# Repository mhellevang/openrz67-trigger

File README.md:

# openrz67-trigger

A Bluetooth remote release for the Mamiya RZ67. A small box on a coin cell plugs into the
camera's remote port. An Android or iPhone app fires the shutter, holds it open for bulb, or
runs a countdown.

## What it does

- Instant release, bulb, and a countdown of 1 to 255 seconds.
- Runs on a CR2032. It sleeps between uses and wakes on a button press.
- Nothing to solder. The board comes assembled from JLCPCB, everything else plugs in.
- Firmware updates over Bluetooth.

## Build one

> **Work in progress.** This board is rev B. It fixes the two known faults in rev A, but is not
> tested yet. For a board that is tested and in use, build the larger ESP32-C3 version at tag
> [`esp32-final`](https://github.com/mhellevang/openrz67-trigger/tree/esp32-final/esp32):
> order the files in
> [`esp32/pcb/archive/2026-09-07-rev2/`](https://github.com/mhellevang/openrz67-trigger/tree/esp32-final/esp32/pcb/archive/2026-09-07-rev2),
> not the rev 3 source. It runs on a LiPo, charges and flashes over USB-C, and works with the
> same apps.

**→ [Build guide](docs/build-guide.md)**: parts, ordering the board, printing the case,
flashing, the camera cable.

In short:

1. Order the assembled board from JLCPCB with the files in [`kicad/out/`](kicad/out/).
2. Print the case from [`case/`](case/).
3. Flash the firmware once with a Raspberry Pi Pico. After that, updates go over Bluetooth.
4. Make the camera cable from a Qwiic pigtail.
5. Install the app.

## Apps

- **Android:** [openrz67-android](https://github.com/mhellevang/openrz67-android), APK on the
  [releases page](https://github.com/mhellevang/openrz67-android/releases/latest).
- **iPhone:** [openrz67-ios](https://github.com/mhellevang/openrz67-ios), built from source in
  Xcode for now.

## Using it

| You do | It does |
|---|---|
| Press the button | Wakes and waits 3 minutes for a phone. The LED blinks every 2 s |
| Open the app | Connects on its own. The LED goes dark |
| Leave it | Stays on while the app is connected. With no phone for 3 minutes, it sleeps |
| Hold the button 3 s | Off, until the next press |

For bulb, set the camera's shutter-speed dial to `B`. The camera closes the shutter by itself
after about 60 seconds.

## What's in here

```
openrz67-trigger/
├── kicad/        # the board, generated from tools/design.py; fab files in out/
├── case/         # 3D-printed case (build123d), shell + sliding floor + light pipe; STLs in stl/
├── firmware/     # Zephyr application for the nRF54L15
└── docs/
    ├── build-guide.md
    ├── protocol.md     # camera port and Bluetooth commands
    ├── perfboard.md    # the same circuit on perfboard, off-the-shelf parts
    ├── support.md      # app help
    ├── privacy.md      # app privacy policy
    ├── render/         # renders docs/img/case-*.png with Blender
    └── notes/          # design history and reasoning
```

Earlier ESP32-C3 versions are at tag
[`esp32-final`](https://github.com/mhellevang/openrz67-trigger/tree/esp32-final/esp32).

## License

[MIT](LICENSE), covering the firmware, the KiCad design files and the enclosure sources. MIT
is written for software, but its grant is broad enough to serve a hardware design;
the closest hardware-specific equivalent is CERN-OHL-P.

The footprints, symbols and 3D models in `kicad/openrz67-nrf.pretty/`,
`openrz67-nrf.kicad_sym` and `openrz67-nrf.3dshapes/` are **not** covered, because they are
not mine to license. They come from the EasyEDA/LCSC part libraries and are redistributed
here for convenience under their originators' terms.

Not affiliated with Mamiya.

## Credits

The camera connector pinout that made this project possible was described to me by
Julio Ryuuzaki, who built and sold the Bluetooth [RZ Blue](https://ryuuzaki.jp/) trigger
for years. He answered a cold email in December 2022 with the essentials: four pins, one
ground, two live, one unconnected. He also warned that the camera closes the shutter by
itself after about a minute in bulb mode. Thank you.

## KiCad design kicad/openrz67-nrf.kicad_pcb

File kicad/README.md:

# Board (KiCad)

KiCad 10 project for the coin-cell trigger: 29.5 × 29 mm, 2 layers, Ebyte E73-2G4M08S1F
(nRF54L15) module, CR2032 clip on the back, two TLP172AM PhotoMOS relays, JST SH 1.0 mm
side-entry camera connector, a second SH connector for SWD, one button, one LED, a P-MOSFET against a reversed cell. No regulator, no charger, no power
switch. Rev A is built and works; the source here is rev B, not ordered. Fab packages that were sent are in [`archive/`](archive/).

The schematic and the board are **generated**: `tools/design.py` holds parts, placement,
nets and every track, and the two generators write the KiCad files from it. Edit the model
and run `tools/regen.sh`; do not edit the `.kicad_sch` / `.kicad_pcb` by hand, the next
run overwrites them.

| File | What |
|---|---|
| `tools/design.py` | the design: parts with LCSC numbers, positions, nets, tracks, vias, keepout |
| `tools/gen_sch.py` | writes `openrz67-nrf.kicad_sch`: one symbol per part, a global label on every used pin, a no-connect on every unused one |
| `tools/gen_pcb.py` | writes `openrz67-nrf.kicad_pcb` with pcbnew: footprints, nets, outline, GND pours, antenna keepout, tracks, design rules |
| `tools/regen.sh` | runs both generators, then exports everything in `out/` and runs DRC (with schematic parity) and ERC |
| `tools/fetch_3d.sh` | downloads STEP+WRL models for every LCSC part in the BOM into `openrz67-nrf.3dshapes/` |
| `tools/module_3d.py` | box model of the E73 module (none on LCSC or from Ebyte): `uv run tools/module_3d.py` |
| `tools/export_step.sh` | board STEP to `out/openrz67-nrf.step` (gitignored); fetches missing part models first |
| `openrz67-nrf.3dshapes/` | 3D models; `.wrl` committed (renders), `.step` gitignored except the module's |
| `openrz67-nrf.kicad_sym`, `openrz67-nrf.pretty/` | project libraries: LCSC/EasyEDA imports via easyeda2kicad and KiCad's `R` |
| `out/` | generated: Gerber+drill zip, position file, BOM with LCSC numbers, schematic PDF, top/bottom renders, DRC/ERC reports |

## Regenerate

Only needed to change the board. The files to order one are already in `out/`.

```sh
tools/regen.sh
```

Close KiCad first. Needs KiCad 10: `kicad-cli`, and a python that has KiCad's `pcbnew` module.
On macOS the script finds both in `/Applications/KiCad`. Elsewhere, give it the full paths. On
Linux that is usually:

```sh
KICAD_CLI=/usr/bin/kicad-cli KICAD_PY=/usr/bin/python3 tools/regen.sh
```

It exits non-zero on any DRC/ERC error or unconnected pad.

## Circuit

The cell (`VBAT`) feeds the module through `Q1`, an AO3401A P-MOSFET with its drain on the
clip, source on `VDD` and gate on GND. The right way round the body diode conducts until the
channel turns on (under 85 mΩ at V<sub>GS</sub> = −2.5 V, about 1 mV at 15 mA). A cell put in upside
down leaves it off, so `VDD` never goes negative. The module has one supply pad (9, 1.8–3.6 V
per Ebyte; the nRF54L15 itself starts at 1.75 V) and both crystals inside. 100 µF sits at the clip terminal, ahead of `Q1` (a ceramic, a reversed cell does not harm it),
100 nF right at module pad 9 (`C3`, ground straight to pad 10) and 100 nF at `Q1`/SWD (`C2`).
Each PhotoMOS LED is driven from a GPIO through 220 Ω: about 4 mA at 2.7 V with the worst-case
LED forward voltage, the TLP172AM needs up to 3 mA. The status LED has 1 kΩ (about 1 mA).
With a fresh cell both relays and the LED draw about 14 mA, inside Nordic's recommended 15 mA
sustained total for all GPIOs.
The PhotoMOS outputs go to the camera connector; camera ground (`CAM_GND`)
is a separate net from the cell's `GND`. `J1` has the camera port's pin order, so the camera
cable is wired straight through. Pigtail wire colours vary; go by pin position, pin 1 is next
to the white dot.

| nRF54L15 | Module pad | Function |
|---|---|---|
| P1.04 | 7 | button to GND, internal pull-up, wake from System OFF |
| P2.00 | 18 | status LED through 1 kΩ |
| P2.04 | 27 | S1 PhotoMOS LED through 220 Ω |
| P2.05 | 28 | S2 PhotoMOS LED through 220 Ω |
| SWCLK / SWDIO | 11 / 12 | `J2` pins 3 / 4 |
| nRESET | 19 | not brought out; reset over SWD |

The button has to be on P0 or P1: P2 cannot wake the chip from System OFF. The two relay outputs run
at high drive (S0H1) for the 4 to 7 mA the PhotoMOS LEDs draw. The left pad column faces the board
edge; `VDD` (pad 9) and the button (pad 7) leave it on two tracks between the module and the edge.

Connectors:

| Ref | Pin | Signal |
|---|---|---|
| `J1` camera, SH 1.0 mm (Qwiic/STEMMA QT cable) | 1 | not connected (camera 6 V) |
| | 2 | camera ground |
| | 3 | S1 |
| | 4 | S2 |
| `J2` SWD, SH 1.0 mm (Qwiic cable to the probe) | 1 | GND |
| | 2 | VDD. With the cell out, the probe's 3.3 V powers the board here. Never with the cell in: it would charge the CR2032 |
| | 3 | SWCLK |
| | 4 | SWDIO |

## Design rules

Clearance 0.127 mm, min track 0.127, default track 0.20 (signals 0.16, power 0.25), via
0.45/0.25, hole-to-track 0.175, hole-to-hole 0.30, copper-to-edge 0.30, mask expansion
0.051. JLCPCB silkscreen minimums (1.0 mm text, 0.15 mm line). A rule area over the
module antenna (x 0–15, y 0–5.3) keeps copper, tracks and vias off both layers.

DRC and ERC report 0 errors and 0 warnings; the reports are in `out/`.

## Mechanical

Outline 29.5 × 29 mm, R0.8 corners, no mounting holes. All parts on top except the cell clip
on the back. Module antenna end is flush with the top edge (y = 0); both SH connectors sit along the
bottom edge with their mouths facing it (y = 29), SWD left of camera (the SWD cable is a
lid-off job, no wall opening); the button sits bottom-left, the LED between the two connectors.

| Part | Height over the board |
|---|---|
| CR2032 clip `BT1` (back) | 3.75 mm, the cell under it; cell centre (13.5, 18), slides in from either long side |
| `J1` camera and `J2` SWD connectors | 2.9 mm, body 6.0 × 4.3 each |
| Module `U1` | 2.4 mm (Ebyte drawing) |

`BT1` is only the positive clip (MYOUNG drawing: "TERMINAL(+)"). The cell's negative face
rests on the Ø10 mm pad in the middle of the back. The pad gets solder paste through a Ø7 mm
stencil opening, so it carries a solder dome, and there is no copper of any kind on the back
from the pad's edge out to 10.2 mm from the cell centre. The solder mask is open out to 9 mm,
past the cell's minus face, so that face has only bare laminate around the pad, a copper
thickness lower than the pad. Two GND vias sit in the pad outside the paste, 4.3 mm from the
centre, and tie it to the top GND. The holder footprint's silkscreen inside that circle is
removed. Ebyte's manual gives no antenna keepout figure; the rule area covers the
PCB antenna (the module's top 5.2 mm) plus 2 mm to its right. The module's 3D model is a plain box from
`tools/module_3d.py`: blue PCB with the antenna, grey shield.

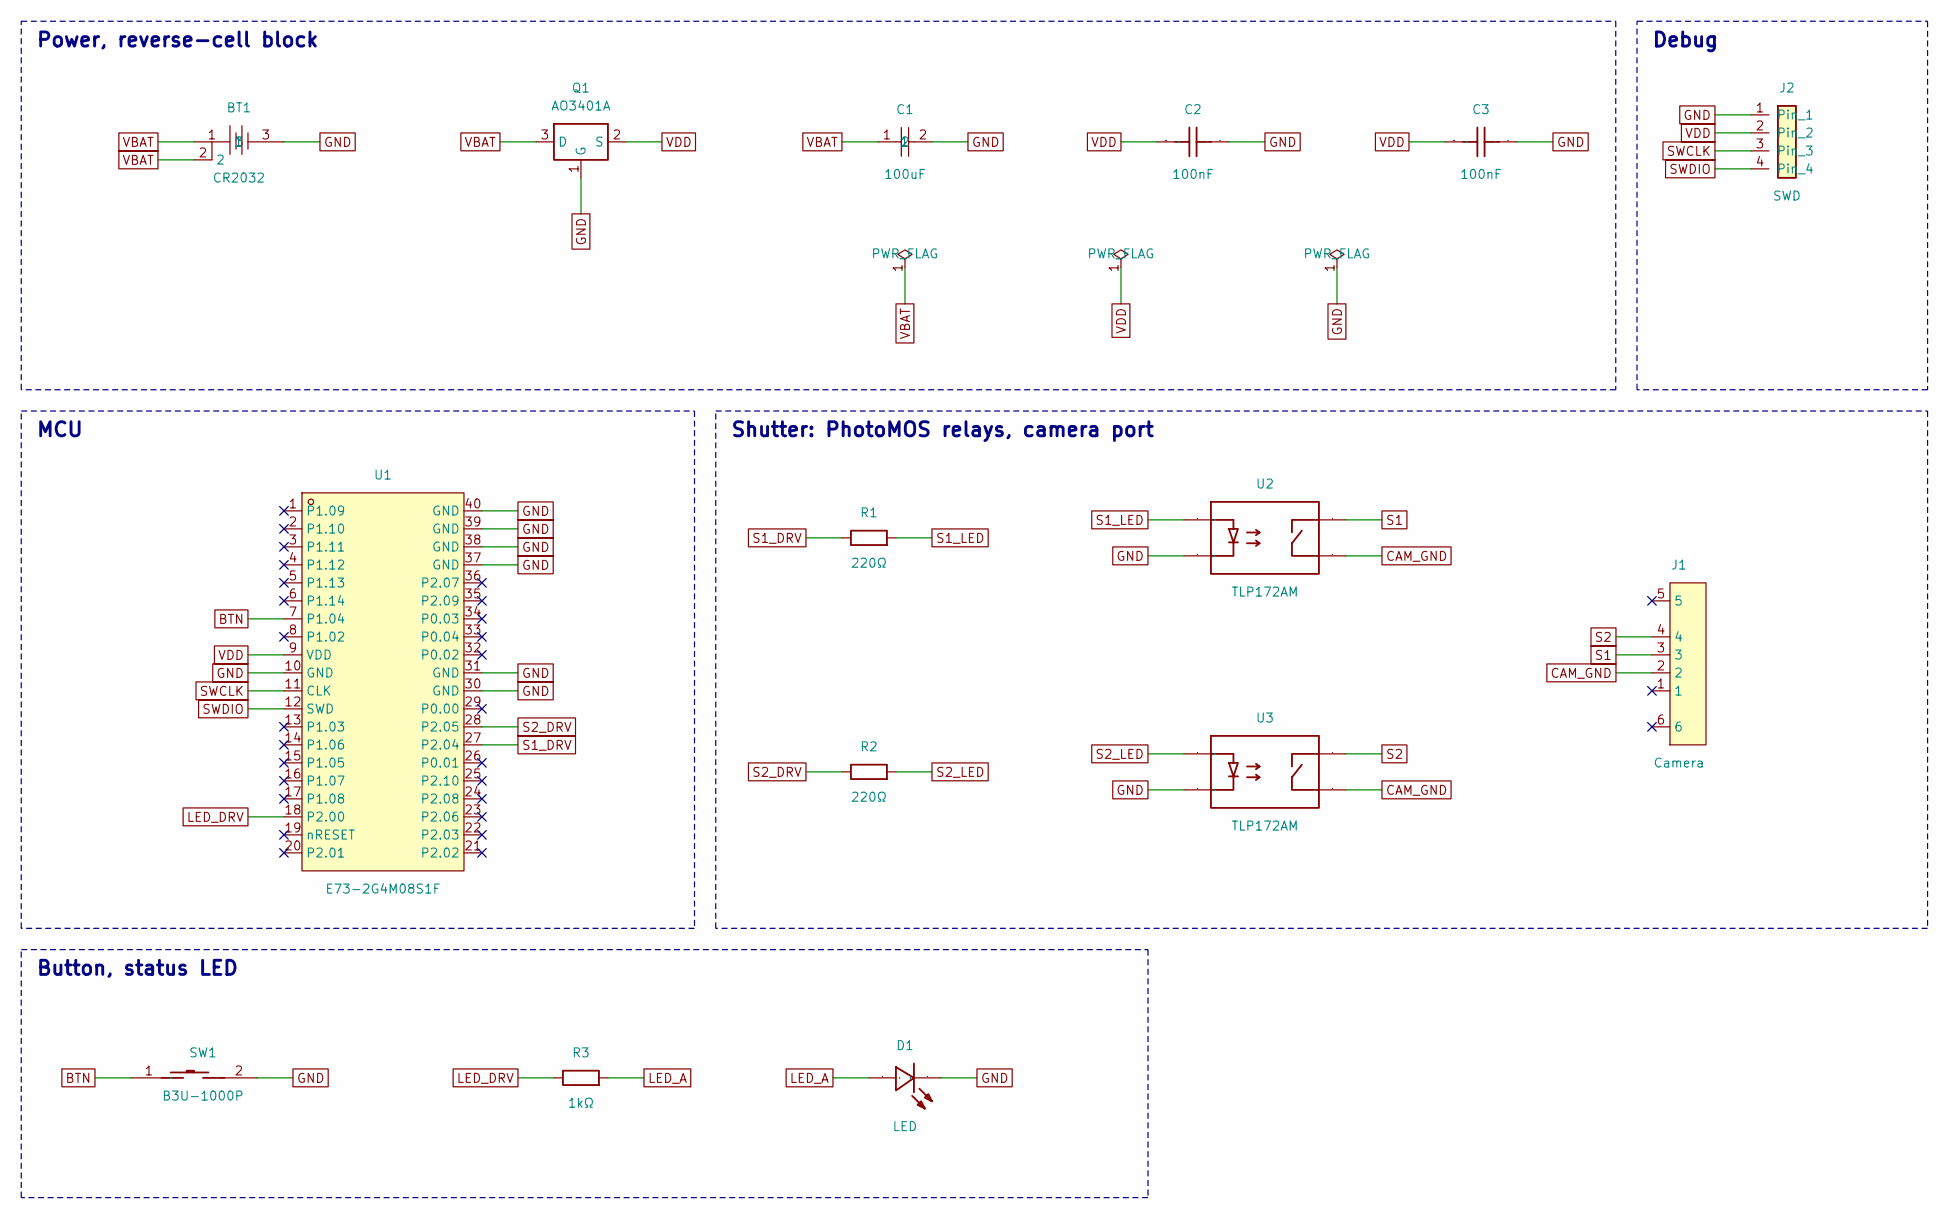
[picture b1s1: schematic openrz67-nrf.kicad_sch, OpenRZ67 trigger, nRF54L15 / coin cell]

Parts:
BT1: CR2032; BAT-SMD_MY-2032-16; MPN MY-2032-16; LCSC C2902340
C1: 100uF; C1206; MPN CL31A107MQHNNNE; LCSC C15008
C2, C3: 100nF; C0402; MPN CL05B104KO5NNNC; LCSC C1525
D1: LED; LED0603-RD; MPN KT-0603R; LCSC C2286
J1: Camera; CONN-SMD_4P-P1.00_SM04B-SRSS-TB-LF-SN; MPN SM04B-SRSS-TB(LF)(SN); LCSC C160404
J2: SWD; CONN-SMD_4P-P1.00_SM04B-SRSS-TB-LF-SN; MPN SM04B-SRSS-TB(LF)(SN); LCSC C160404
Q1: AO3401A; SOT-23; MPN AO3401A; LCSC C15127
R1, R2: 220Ω; R0402; MPN 0402WGF2200TCE; LCSC C25091
R3: 1kΩ; R0402; MPN 0402WGF1001TCE; LCSC C11702
SW1: B3U-1000P; KEY-SMD_B3U-1000PM; MPN B3U-1000P; LCSC C231329
U1: E73-2G4M08S1F; WIRELM-SMD_E73-2G4M08S1F; MPN E73-2G4M08S1F; LCSC C54337734
U2, U3: TLP172AM; SMD-4_L4.6-W3.7-P2.54-LS7.0-BR; MPN TLP172AM(TPL,E); LCSC C2152276

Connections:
BTN: SW1.1, U1.7 (P1.04)
CAM_GND: J1.2, U2.3 (D), U3.3 (D)
GND: BT1.3, C1.2, C2.2, C3.2, D1.1 (K), J2.1, Q1.1 (G), SW1.2, U1.10 (GND), U1.30 (GND), U1.31 (GND), U1.37 (GND), U1.38 (GND), U1.39 (GND), U1.40 (GND), U2.2 (K), U3.2 (K)
LED_A: D1.2 (A), R3.2
LED_DRV: R3.1, U1.18 (P2.00)
S1: J1.3, U2.4 (D)
S1_DRV: R1.1, U1.27 (P2.04)
S1_LED: R1.2, U2.1 (A)
S2: J1.4, U3.4 (D)
S2_DRV: R2.1, U1.28 (P2.05)
S2_LED: R2.2, U3.1 (A)
SWCLK: J2.3, U1.11 (CLK)
SWDIO: J2.4, U1.12 (SWD)
VBAT: BT1.1, BT1.2, C1.1, Q1.3 (D)
VDD: C2.1, C3.1, J2.2, Q1.2 (S), U1.9 (VDD)

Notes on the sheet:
Power, reverse-cell block
Debug
MCU
Shutter: PhotoMOS relays, camera port
Button, status LED

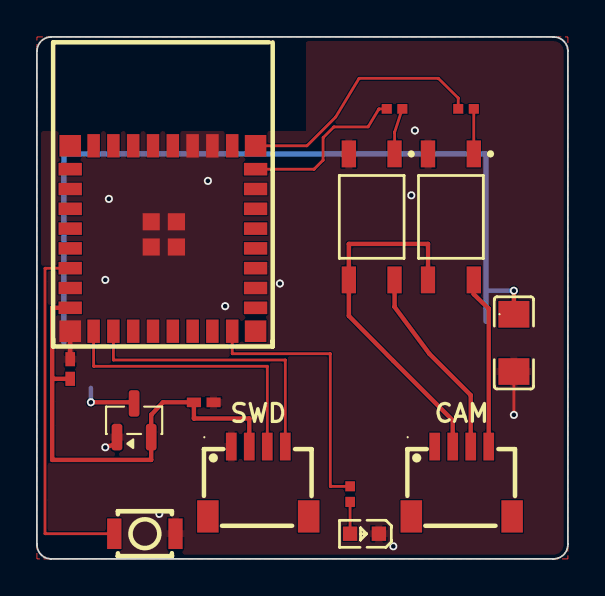
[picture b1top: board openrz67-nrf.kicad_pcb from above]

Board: 2 copper layers, 29.5 x 29.0 mm, 15 parts (1 on the bottom side), 15 nets.

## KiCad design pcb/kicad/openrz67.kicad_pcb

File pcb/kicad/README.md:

# openrz67 PCB — KiCad project

KiCad 10 project for the OpenRZ67 trigger board (48 × 22 mm, 2 layers, ESP32-C3,
two TLP172AM PhotoMOS relays, LGS5500 charger/boost). This is now the **source**; the EasyEDA Pro
project it was ported from is archived in `../archive/easyeda/` (v2 `.epro` and v3 `.epro2`);
the fabricated 2025-09-23 revision (Gerber, BOM, PnP, STEP) is in `../archive/2025-09-23-rev1/`.

| File | What |
|---|---|
| `openrz67.kicad_pro/.kicad_sch/.kicad_pcb` | project, schematic (1 sheet), board |
| `openrz67.kicad_sym`, `openrz67.pretty/` | symbols and footprints as imported from EasyEDA/LCSC (project-local libs) |
| `tools/regen.sh` | rebuilds everything in `out/` in one go; run it after any change to the board or schematic |
| `tools/post_import.py` | design rules, net classes, zone settings, layer names. **Authoritative**: it overwrites `openrz67.kicad_pro`, so rule changes made in Board Setup are reverted on the next run. Edit the values in the script. Rewrites the board in place, so close KiCad first. Idempotent. |
| `tools/fetch_3d.sh` | downloads STEP+WRL models for every LCSC part into `openrz67.3dshapes/` (uses `easyeda2kicad`, `uvx`, `pipx` or a local venv, whichever exists) |
| `tools/export_step.sh` | board STEP to `out/openrz67.step` (gitignored, ~20 MB); fetches missing part STEPs first |
| `openrz67.3dshapes/` | 3D models; `.wrl` committed (render), `.step` gitignored (fetch when you need a board STEP) |
| `out/` | generated: Gerber+drill zip, position file, BOM (with LCSC numbers), schematic PDF, top/bottom renders, ERC/DRC reports |

## Regenerate outputs

Everything in `out/` is generated. Rebuild all of it with one command, so the
committed outputs and the check reports always describe the committed sources:

```sh
tools/regen.sh
```

It runs `post_import.py`, exports Gerbers, drill files and their maps, zips them,
writes the position file, the BOM, the schematic PDF and the two board renders,
then runs DRC with schematic parity and ERC. It exits non-zero on errors;
warnings are printed and accepted (see below). Close KiCad first: `post_import.py`
rewrites the board and the project file in place.

Override the tool paths if KiCad is not in the macOS default location:

```sh
KICAD_CLI=/usr/bin/kicad-cli KICAD_PY=/usr/bin/python3 tools/regen.sh
```

## Design rules (from the EasyEDA project)

Clearance 0.127 mm (EasyEDA pour-to-track minimum; track-to-track was 0.152), min track
0.127, default track 0.16, via 0.45/0.20 (min 0.40/0.20), hole-to-track 0.175,
hole-to-hole 0.30, solder-mask expansion 0.051, thermal spoke 0.254 / gap 0.152.
Net classes: `gnd` (GND, 0.13 track), `3v` (VCC, 0.20), `5v` (+5V, 0.254 track, 0.5/0.3 via).
Copper-to-edge clearance is 0.30 mm (JLCPCB recommendation; the original pours ran to
the outline). Silkscreen minimums are JLCPCB's: 1.0 mm text height, 0.15 mm line width.

## Accepted warnings

ERC is clean: **0 errors, 0 warnings**. DRC has no errors; the warnings below are known,
understood and left in the reports rather than silenced, so a genuinely new one stands
out. No DRC or ERC exclusions are configured.

| Check | Count | What |
|---|---|---|
| `courtyards_overlap` | 5 | Neighbours closer than 0.1 mm on the fabricated rev-1 layout: C21/USB1, L3 against C20/R9/R12, H1/USB1. |
| `text_height`, `text_thickness` | 2 | The `BOOT EN` label on F.SilkS is 0.5 mm / 0.10 mm, under JLCPCB's 1.0 mm / 0.15 mm. Enlarged in place it runs over the R18 pads and the S3 body, where the fab clips silkscreen against solder mask. Splitting it into separate `BOOT` and `EN` labels does not help: the free band above the S1 pads is 0.85 mm and the one below the switches is 0.7 mm, both under the 1.0 mm the text needs. Fixing it means moving parts. Every other silkscreen text is at or above 1.067 mm. |

## Rev 2 layout changes (2026-09-03)

Outline unchanged from rev 1: **48 × 22 mm**, 2 mm corner radius, mounting holes at
(2, 20) and (46, 2). Edges are named here by their landmark, because the enclosure in
`../../case/` measures Y from the opposite side: the **USB-C end** is x = 0, the
**camera end** is x = 48, the **S3 edge** is y = 0, and the **switch edge** is y = 22.

- **U4** camera connector: side-entry S4B-XH-A (LCSC C157925) at (44.3, 11.0), opening
  out of the camera end.
- **BAT1** battery connector: vertical through-hole **B2B-PH-K-S(LF)(SN)** (LCSC C131337)
  on the **top** side, restored on 2026-09-05 from the layout before `d7d51ae`.
  Centre (3.275, 4.8105), rotation 90°. Pin 1 = BAT+, pin 2 = GND.
  The original 0.635 mm top-side BAT+ connection and five GND stitching vias are restored;
  the bottom-side BAT+ branch and its transfer via are removed. `BAT+` / `BAT-` labels
  on the bottom identify the through-hole solder pads. All components are now on top.
  The battery cable must reach around the board if the cell remains underneath.
- **Shutter outputs are PhotoMOS, not relays (2026-09-04).** K1/K2 (G6K-2F-Y), their DTC114E
  drivers Q1/Q2, flyback diodes D1/D2 and coil decoupling C27/C28 are gone. Each channel is one
  **TLP172AM** (Toshiba, LCSC C2152276, 4-pin SO6): the ESP32 GPIO drives the LED through a
  **220 Ω** 0402 (R21/R22, C25091), about 9 mA nominal. At 3.3 V, VOH = 0.8 × VDD,
  VF = 1.4 V and +1% resistance give 5.6 mA at 25 °C, within the datasheet's 5 to 25 mA
  recommendation. The MOSFET output closes S1/S2 to camera ground.
  TLP172AM replaced TLP172GM on 2026-09-05: maximum on-resistance is 2 Ω at 25 °C / IF = 5 mA,
  versus 50 Ω continuous for GM. AM's output rating is 60 V / 500 mA; package and pin functions
  are unchanged. The imported pad numbering 1/2/3/4 maps to Toshiba pins 1/3/4/6.
  Firmware activates S1, waits 10 ms, then activates S2. Camera input limits remain unverified;
  test the assembled prototype before ordering a production batch. See [research notes](notes/rz67-remote-inputs.md)
  and the [Toshiba datasheet](https://toshiba.semicon-storage.com/info/docget.jsp?did=36714&prodName=TLP172AM).
  U5 = S1 (net `S1_DRV`, **GPIO4**, U1 pin 9), U6 = S2 (net `S2_DRV`, GPIO3, U1 pin 8). Rev 1
  drove S1 from GPIO21, which is U0TXD: the ROM boot log leaves it high until `setup()` runs,
  so S1 was closed during every boot. Harmless alone, since the camera needs S1 and S2 together,
  but GPIO4 is a plain input at reset and GPIO21 is now free for serial logging. Isolation is kept: camera ground `AGND` still touches only U4 pin 2 and the two
  output pins, and the AGND pours (both layers) were pulled in from x = 32.1 to x = 34.6 so the
  LED side of each part sits in the GND domain. Eight parts became four, the tallest top-side part
  went from 5.2 mm (relay) to 2.2 mm, and the coil current (about 67 mA while an exposure is
  held) is gone. Footprint `SMD-4_L4.6-W3.7-P2.54-LS7.0-BR` and the 3D model came from
  `easyeda2kicad` for C261926; the unused relay/SOT-346/SOD-523 footprints, models and symbols
  were removed from the project libraries. R4/R5 (USB 22 Ω) are UNI-ROYAL 0402WGF220JTCE
  (C25092, JLCPCB Basic) since JLCPCB had 2 of the Yageo part in stock.
- **C5** moved to the analog supply: the 100 nF that sat on VCC next to the ferrite bead
  L2 now sits on the far side of it, on the new **VDDA** net feeding U1 pins 31/32 (radio and
  ADC supply). Before, nothing decoupled that net; the bead alone was just series impedance.
  VCC reaches L2 pin 1 through a new via beside the pad. Same part, same position, no BOM
  change. B.Cu ground under U1 stays one region (648.7 mm²).
- **Under-board clearance** the enclosure has to provide, from the datasheets:

  | What | Height below the board |
  |---|---|
  | BAT1 through-hole tails, B2B-PH-K-S | 3.4 mm unclipped |
  | S3 through-hole tails, B2B-PH-K-S | 3.4 mm unclipped |
  | U4 through-hole tails, S4B-XH-A | 3.4 mm unclipped |
  | USB1 shell posts | ~1 mm |

  The cell can only sit against the board if those tails are **clipped flush**. Budget
  3.4 mm otherwise. A foam pad between cell and board is still wanted, but 1.5 mm of it
  only fits after clipping.

**Removed again:** an earlier attempt widened the board to 25 mm for an unpopulated 1×3
expansion header (GPIO4 / 3V3 / GND) along the switch edge. It was reverted. Reaching the
new edge strip forced the GPIO4 return path across the bottom pour, which split the B.Cu
ground under U1 and LDO1 into two islands and displaced three stitching vias next to the
antenna trace. One GPIO, on a header that was not going to be populated, did not pay for
that. There is no room on this outline for a through-hole header: a hole needs both layers
clear at once, and only two isolated spots on the whole board qualify. Bottom-side solder
pads do fit, but the cell now occupies the bottom. Revisit it together with the enclosure.

## Ordering

`out/gerber/` is tracked unpacked, so a revision's copper is diffable in git.
`tools/regen.sh` also writes `out/openrz67-gerber.zip`, which is what you upload;
it is gitignored because it is one command away and would otherwise churn the
history as a binary blob on every regen. When a revision is actually ordered, copy
the zip, BOM and position file into `../archive/<date>-rev<n>/` as the record of
what was fabricated.

JLCPCB's uploader asks you to map columns; the exports do not use its header names:

| JLCPCB field | Column in `out/openrz67-bom.csv` |
|---|---|
| Comment | `Value` |
| Designator | `Designator` |
| Footprint | `Footprint` |
| LCSC Part # | `LCSC` |

The position file is rewritten by `regen.sh` into JLCPCB's CPL layout (`Designator, Mid X,
Mid Y, Layer, Rotation`, mm suffix); their parser rejects KiCad's native header with
"Failed processing the CPL file". Origin is the drill-file origin at the board's top-left
corner, the same convention JLCPCB accepted for rev 1, and rotations for the top-side
parts are unchanged since that order. BAT1 is back on top with its original through-hole
footprint and rotation. Check BAT1 pin 1 in the fab's assembly preview before confirming.
No bottom-side component assembly is needed. BAT1, S3 and U4 are through-hole parts;
confirm the assembler's through-hole service or hand-solder them after SMD assembly.

## Port notes (2026-09-03)

- Import path: EasyEDA Pro **v2** `.epro` → KiCad "Import Non-KiCad Project". The v3
  `.epro2` export loads as an empty board in KiCad 10.0.6.
- Removed the "JeefunPCB" A3 sheet-frame symbol that came with the EasyEDA template
  and replaced it with a KiCad title block. Annotated the 62 power flags (`#PWR001…`),
  deleted two floating GND flags, added a no-connect on U4 pin 1.
- EasyEDA local labels became global labels so net names match the board (`BAT+`, `D7`, and the
  Wemos-style `D1`/`D6`, renamed `S2_DRV`/`S1_DRV` on 2026-09-04); EasyEDA auto-nets (`$1N…`) were renamed to KiCad's `Net-(…)` names.
  Connectivity was verified pad-for-pad against the schematic netlist before renaming.
- USB-C shell pads 13/14 are GND in the schematic; the EasyEDA board had them net-less.
  They are GND now (they sit in the GND pour).
- Schematic footprint fields for L2 (L0603→L0402), U1 (TL→BL QFN variant) and
  R18 (R0603→R0402) were corrected to what is actually on the board.
- DRC: 0 errors, 0 unconnected, schematic parity clean. Remaining warnings are silk
  overlaps/courtyards from the LCSC footprints. Two dangling vias (+5V_VIN, a duplicated
  VCC via) and a 0.1 mm track stub from the original layout were removed. Two small USB1
  polygons that the importer put on Edge.Cuts (not in the EasyEDA outline) moved to F.Fab.
- Gerber check against the fabricated 2025-09-23 set: copper and mask match apart from
  U4 (now S4B-XH-A side-entry instead of B4B-XH-A) and pour-fill details after KiCad's
  refill (thermal shapes); silkscreen differs in font rendering only.
- 3D models: the importer left dangling `EASYEDA_MODELS/…` references. Models were fetched
  per LCSC number with `easyeda2kicad` (`tools/fetch_3d.sh`) and both the board footprints and
  the library `.kicad_mod` files repointed to `openrz67.3dshapes/<name>.wrl`, keeping the
  importer's offsets/rotations, so "Update Footprints from Library" does not undo it. Board STEP:
  `kicad-cli pcb export step --subst-models -o out/openrz67.step openrz67.kicad_pcb`
  (needs the `.step` files, run `tools/fetch_3d.sh` first).
- Bottom silkscreen label changed from "EPS32-C3 Camera Trigger V1.0 / 2025-08-23" to
  "OpenRZ67 Trigger v2 / 2026-09".
- Pin electrical types were set by hand for the ICs (ESP32-C3, LGS5500, ME6211, USB-C);
  passives, connectors and the PhotoMOS pins are `passive`. Supply nets without a driver carry `PWR_FLAG`
  (GND, AGND, BAT+, VBUS, +5V_VIN, VDDA). ERC runs at default severities: 0 errors, 0
  warnings. The eight dangling wire ends inherited from the EasyEDA drawing were removed
  (an orphan S1/S2/AGND label cluster and three over-long wire tails); the netlist is
  unchanged, verified node-for-node before and after.
- The two mounting holes are real footprints (`MountingHole_2.0mm_Pad3.0`, plated 3.0 mm pad,
  2.0 mm drill) with `MountingHole` symbols H1/H2 in the schematic (excluded from BOM/POS).
- Courtyards were regenerated as pad/body bounding boxes (+0.05 mm) — the LCSC ones were
  oversized. Silkscreen outlines of 0402/0603 parts and of the two overhanging connectors
  (USB-C, U4) live on F.Fab now. DRC: 0 errors, 6 courtyard warnings where neighbours are
  closer than 0.1 mm on the fabricated layout (C28/S3, C21/USB1, L3 vs C20/R9/R12, H1/USB1).
- The library symbol file was pruned to the symbols in use; the schematic's embedded copies are
  regenerated from it, so "symbol differs from library" warnings are gone.

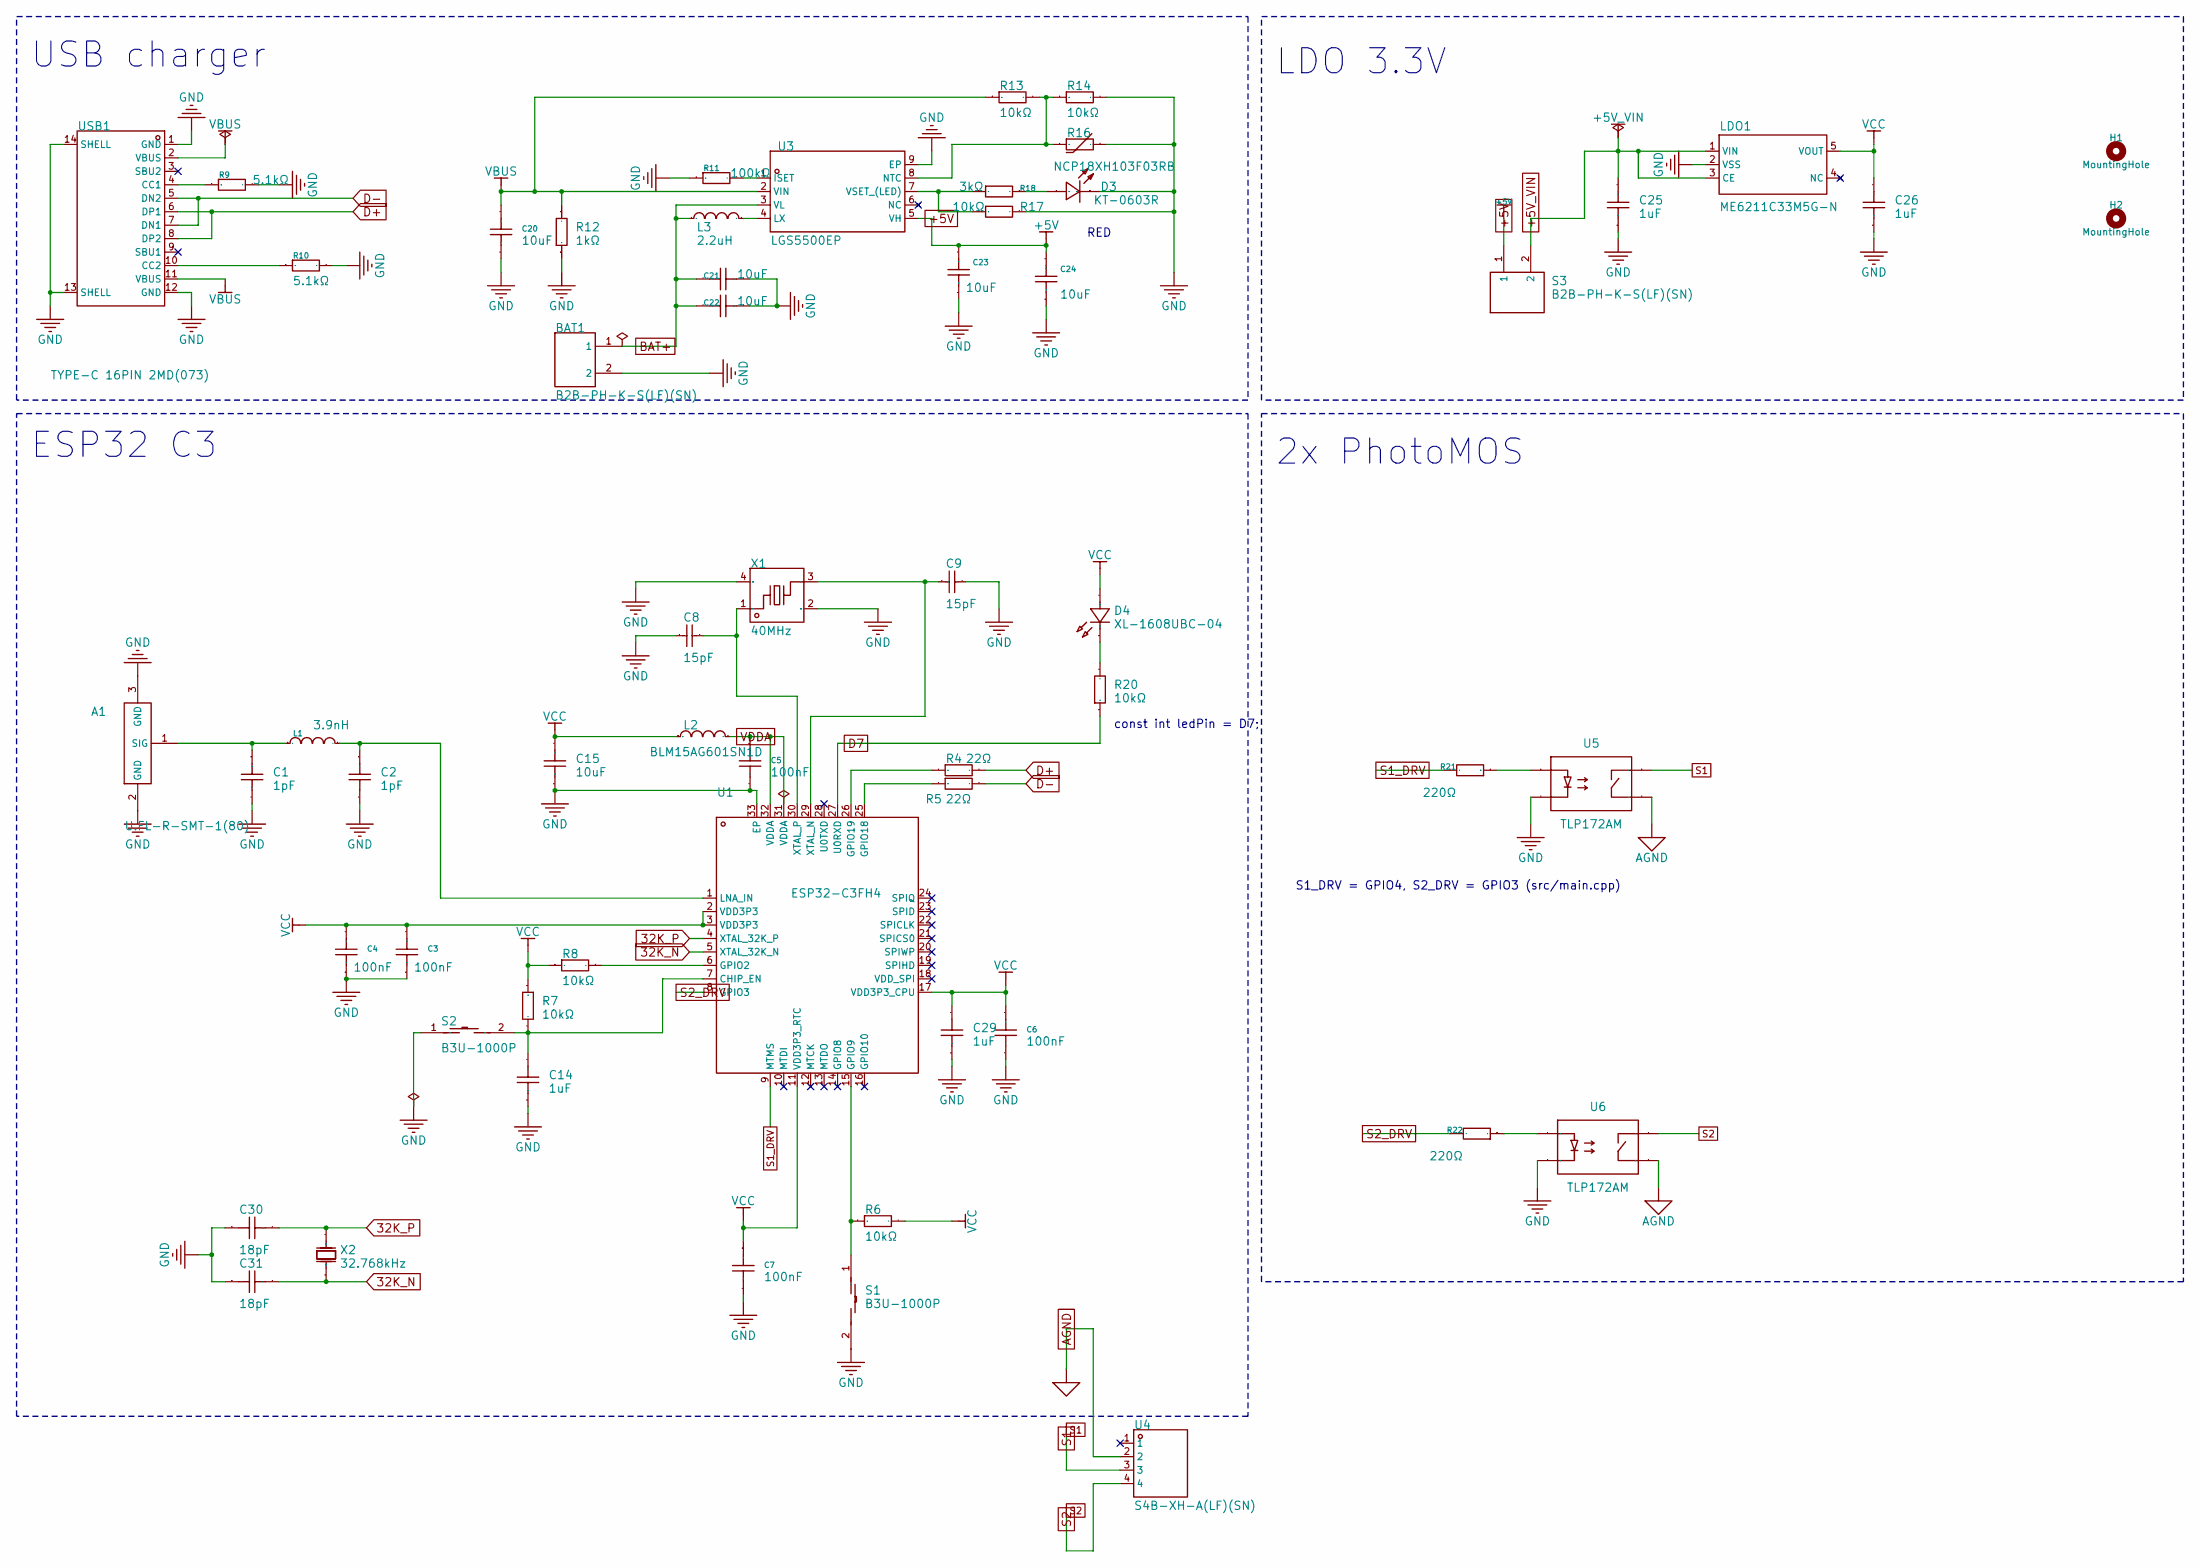
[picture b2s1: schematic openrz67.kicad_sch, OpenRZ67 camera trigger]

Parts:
A1: U.FL-R-SMT-1(80); RF-SMD_FRF05002-JSS103M; Manufacturer Part U.FL-R-SMT-1(80); LCSC Part Name IPEX 内针
BAT1: B2B-PH-K-S(LF)(SN); CONN-TH_B2B-PH-K-S; Manufacturer Part B2B-PH-K-S(LF)(SN); LCSC Part Name 1x2P 间距:2mm 直插 系列:PH
C1, C2: 1pF; C0402; Manufacturer Part CC0402CRNPO9BN1R0; LCSC Part Name 1pF 50V
C3, C4, C5, C6, C7: 100nF; C0402; Manufacturer Part GRM155R71H104KE14D; LCSC Part Name 100nF ±10% 50V
C8, C9: 15pF; C0402; Manufacturer Part GJM1555C1H150FB01D; LCSC Part Name 15pF ±1% 50V
C14, C25, C26, C29: 1uF; C0603; Manufacturer Part CGA0603X5R105K500JT; LCSC Part Name 1uF ±10% 50V
C15, C20, C21, C22, C23, C24: 10uF; C0603; Manufacturer Part CL10A106MA8NRNC; LCSC Part Name 10uF ±20% 25V
C30, C31: 18pF; C0402; Manufacturer Part GRM1555C1H180FA01D; LCSC Part Name 18pF ±1% 50V
D3: KT-0603R; LED0603-RD; Manufacturer Part KT-0603R; LCSC Part Name 0603 红灯 高亮
D4: XL-1608UBC-04; LED0603-RD_BLUE; Manufacturer Part XL-1608UBC-04; LCSC Part Name XL-1608UBC-04
H1, H2: MountingHole; MountingHole_2.0mm_Pad3.0
L1: 3.9nH; L0402; Manufacturer Part LQG15HS3N9S02D; LCSC Part Name 3.9nH
L2: BLM15AG601SN1D; L0402; Manufacturer Part BLM15AG601SN1D; LCSC Part Name 单路 0402磁珠 阻抗600Ω@100MHz
L3: 2.2uH; IND-SMD_L7.1-W6.5-P5.60; Manufacturer Part SPM6530T-2R2M; LCSC Part Name 2.2uH ±20% 8.4A
LDO1: ME6211C33M5G-N; SOT-23-5_L3.0-W1.7-P0.95-LS2.8-BL; Manufacturer Part ME6211C33M5G-N; LCSC Part Name 输入6V 输出3.3V 500mA
R4, R5: 22Ω; R0402; Manufacturer Part 0402WGF220JTCE; LCSC Part Name 22Ω ±1% 62.5mW 厚膜电阻
R6, R7, R8, R13, R14, R17, R20: 10kΩ; R0402; Manufacturer Part RC0402FR-0710KL; LCSC Part Name 厚膜电阻 10kΩ ±1% 62.5mW
R9, R10: 5.1kΩ; R0402; Manufacturer Part 0402WGF5101TCE; LCSC Part Name 5.1kΩ ±1% 62.5mW 厚膜电阻
R11: 100kΩ; R0402; Manufacturer Part 0402WGF1003TCE; LCSC Part Name 100kΩ ±1% 62.5mW 厚膜电阻
R12: 1kΩ; R0603; Manufacturer Part 0603WAJ0102T5E; LCSC Part Name 1kΩ ±5% 100mW 厚膜电阻
R16: NCP18XH103F03RB; R0603; Manufacturer Part NCP18XH103F03RB; LCSC Part Name NCP18XH103F03RB
R18: 3kΩ; R0402; Manufacturer Part 0402WGF3001TCE; LCSC Part Name 3kΩ ±1% 62.5mW 厚膜电阻
R21, R22: 220Ω; R0402; Manufacturer Part 0402WGF2200TCE; LCSC Part Name 220Ω ±1% 62.5mW 厚膜电阻
S1, S2: B3U-1000P; KEY-SMD_B3U-1000PM; Manufacturer Part B3U-1000P; LCSC Part Name 3*2.5*1.6mm 立贴 轻触开关
S3: B2B-PH-K-S(LF)(SN); CONN-TH_B2B-PH-K-S; Manufacturer Part B2B-PH-K-S(LF)(SN); LCSC Part Name 1x2P 间距:2mm 直插 系列:PH
U1: ESP32-C3FH4; QFN-32_L5.0-W5.0-P0.50-BL-EP3.7; Manufacturer Part ESP32-C3FH4; LCSC Part Name ESP32-C3FH4
U3: LGS5500EP; ESOP-8_L4.9-W3.9-P1.27-LS6.0-TL-EP3.3; Manufacturer Part LGS5500EP; LCSC Part Name 1A充电,0.3A同步升压放电,超低待机2uA+的TP5400,ETA9697
U4: S4B-XH-A(LF)(SN); CONN-TH_S4B-XH-A-LF-SN; Current Rating 3A; Voltage Rating 250V; Manufacturer Part S4B-XH-A(LF)(SN); LCSC Part Name 1x4P 间距:2.5mm 弯插 系列:XH
U5, U6: TLP172AM; SMD-4_L4.6-W3.7-P2.54-LS7.0-BR; Manufacturer Part TLP172AM(TPL,E; LCSC Part Name TLP172AM(TPL,E
USB1: TYPE-C 16PIN 2MD(073); USB-C-SMD_TYPE-C-6PIN-2MD-073; Manufacturer Part TYPE-C 16PIN 2MD(073); LCSC Part Name Type-C 母 卧贴
X1: 40MHz; CRYSTAL-SMD_4P-L2.0-W1.6-BL-2; Manufacturer Part T201640MFBDE2X; LCSC Part Name 40MHz ±10ppm 12pF
X2: 32.768kHz; CRYSTAL-SMD_L3.2-W1.5-1; Manufacturer Part XKXGI-SUA-32.768K; LCSC Part Name YST310S 32.768KHZ 2P 3215 12.5PF ±20PPM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

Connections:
32K_N: C31.2, U1.5 (XTAL_32K_N), X2.1 (OSC1)
32K_P: C30.2, U1.4 (XTAL_32K_P), X2.2 (OSC2)
+5V: C23.2, C24.2, S3.1, U3.5 (VH)
+5V_VIN: C25.2, LDO1.1 (VIN), LDO1.3 (CE), S3.2
AGND: U4.2, U5.3 (D), U6.3 (D)
BAT+: BAT1.1, C21.2, C22.2, L3.1, U3.3 (VL)
D7: R20.1, U1.27 (U0RXD)
D+: R4.2, USB1.6 (DP1), USB1.8 (DP2)
D-: R5.2, USB1.5 (DN2), USB1.7 (DN1)
GND: A1.2 (GND), A1.3 (GND), BAT1.2, C1.2, C2.2, C3.1, C4.1, C5.2, C6.2, C7.2, C8.1, C9.2, C14.1, C15.1, C20.1, C21.1, C22.1, C23.1, C24.1, C25.1, C26.1, C29.1, C30.1, C31.1, D3.1 (K), LDO1.2 (VSS), R9.2, R10.2, R11.1, R12.1, R14.2, R16.2, R17.2, S1.2, S2.1, U1.33 (EP), U3.9 (EP), U5.2 (K), U6.2 (K), USB1.1 (GND), USB1.12 (GND), USB1.13 (SHELL), USB1.14 (SHELL), X1.2 (GND), X1.4 (GND)
unnamed: A1.1 (SIG), C1.1, L1.1
unnamed: D3.2 (A), R18.2
unnamed: D4.1 (K), R20.2
unnamed: C14.2, R7.2, S2.2, U1.7 (CHIP_EN)
unnamed: R8.2, U1.6 (GPIO2)
unnamed: R6.1, S1.1, U1.15 (GPIO9)
unnamed: R5.1, U1.25 (GPIO18)
unnamed: R4.1, U1.26 (GPIO19)
unnamed: C2.1, L1.2, U1.1 (LNA_IN)
unnamed: C9.1, U1.29 (XTAL_N), X1.3
unnamed: C8.2, U1.30 (XTAL_P), X1.1
unnamed: R11.2, U3.1 (ISET)
unnamed: L3.2, U3.4 (LX)
unnamed: R13.2, R14.1, R16.1, U3.8 (NTC)
unnamed: R17.1, R18.1, U3.7 (VSET_(LED))
unnamed: R21.1, U5.1 (A)
unnamed: R22.1, U6.1 (A)
unnamed: R9.1, USB1.4 (CC1)
unnamed: R10.1, USB1.10 (CC2)
S1: U4.3, U5.4 (D)
S1_DRV: R21.2, U1.9 (MTMS)
S2: U4.4, U6.4 (D)
S2_DRV: R22.2, U1.8 (GPIO3)
VBUS: C20.2, R12.2, R13.1, U3.2 (VIN), USB1.2 (VBUS), USB1.11 (VBUS)
VCC: C3.2, C4.2, C6.1, C7.1, C15.2, C26.2, C29.2, D4.2 (A), L2.1, LDO1.5 (VOUT), R6.2, R7.1, R8.1, U1.2 (VDD3P3), U1.3 (VDD3P3), U1.11 (VDD3P3_RTC), U1.17 (VDD3P3_CPU)
VDDA: C5.1, L2.2, U1.31 (VDDA), U1.32 (VDDA)

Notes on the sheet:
RED
const int ledPin = D7;
USB charger
LDO 3.3V
2x PhotoMOS
ESP32 C3
S1_DRV = GPIO4, S2_DRV = GPIO3 (src/main.cpp)

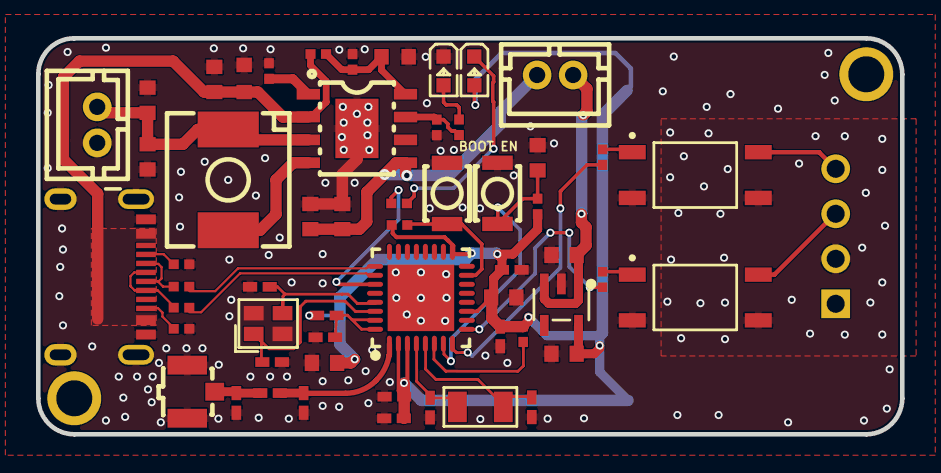
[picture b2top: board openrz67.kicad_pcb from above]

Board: 2 copper layers, 48.0 x 22.0 mm, 59 parts (0 on the bottom side), 36 nets.

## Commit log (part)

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2025-08-18 move countdown logic to esp32
2025-08-31 Finish renaming system outputs to new name
2025-08-31 Update gitignore
2025-09-09 Wip custom esp32-c3 board
2025-09-10 Make BLE work standalone
2025-09-10 Fix reconnect issues
2025-09-11 Debug shutter trigger
2025-09-12 Should trigger D1 too?
2025-09-12 Bulb mode
2025-09-23 Calls to Serial will block boot when no serial is connected, so disable serial via build flags
2025-09-23 Add PCB fabrication files
2025-09-27 Add CPU scaling and fix issues with BLE power settings
2025-09-28 Remove unused debug code
2025-09-28 Cleanup serial prints
2025-09-28 Enabled light sleep. Downscaled CPU to 80Mhz. Added NullStream structure to suppress serial operations in production.
2025-09-28 Added new multi byte BLE protocol for sending user customizable countdown limits from app
2025-09-29 No floor needed
